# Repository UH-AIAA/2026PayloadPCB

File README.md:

# 2026 Payload PCB
This repo stores kicad files and other resources for the 2026 Payload PCB. Once the board is finalized, the repo will be archived.

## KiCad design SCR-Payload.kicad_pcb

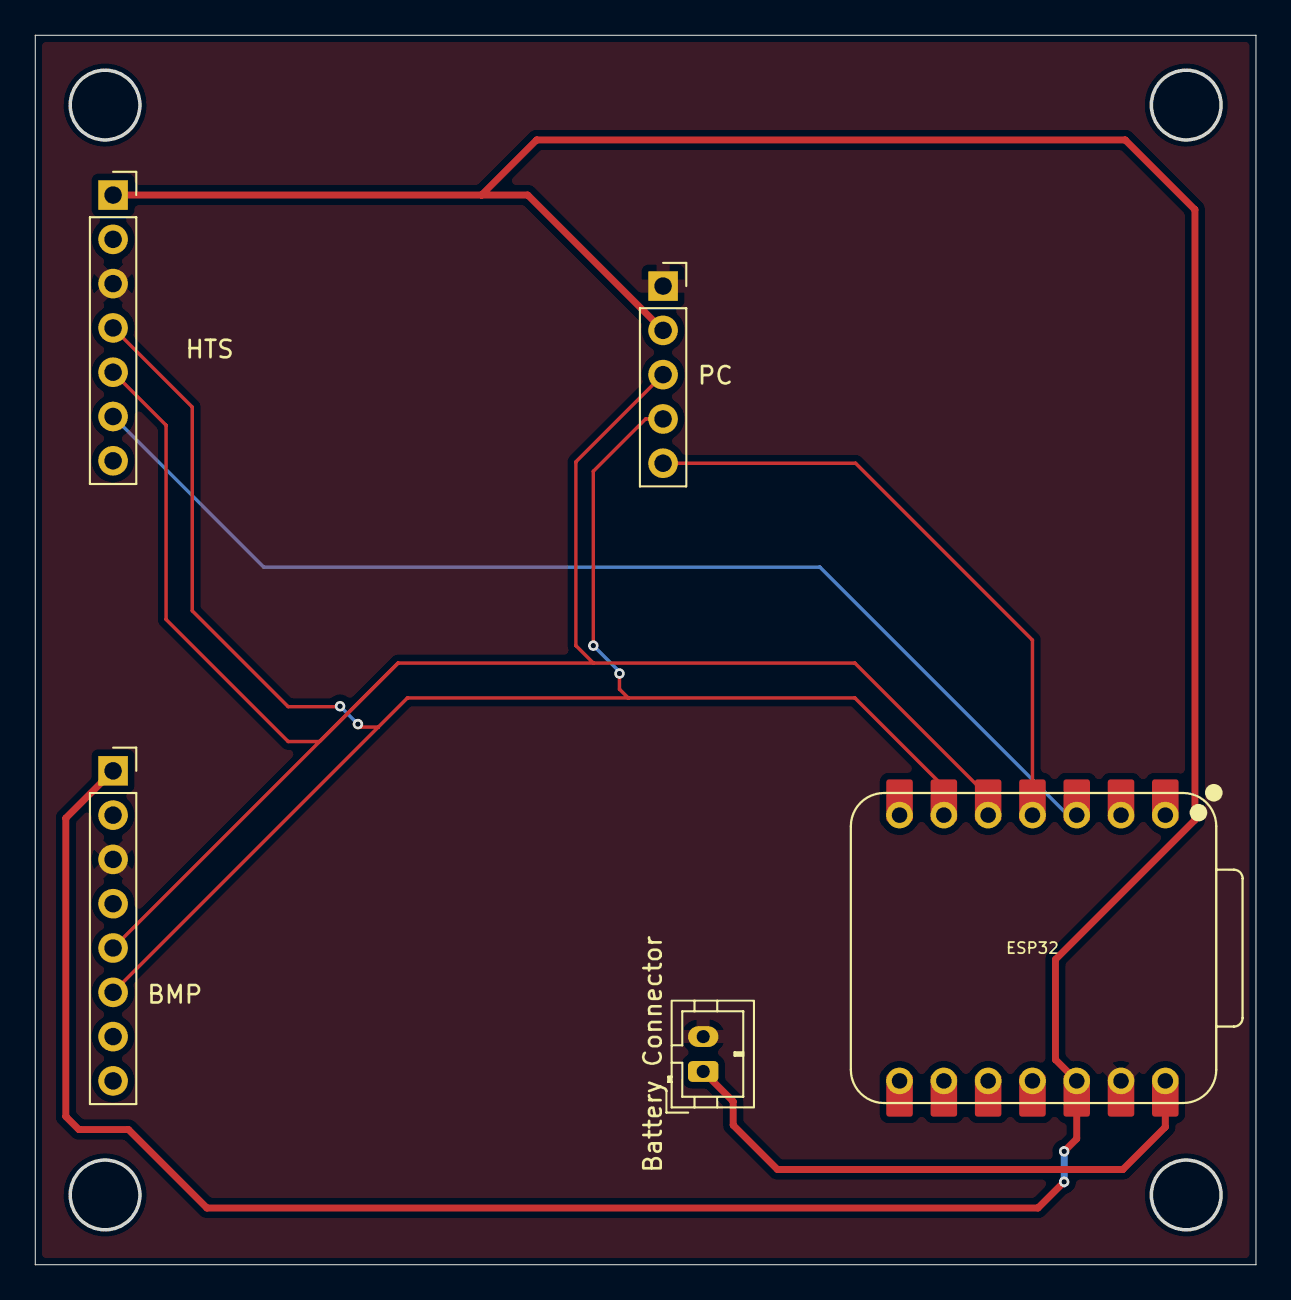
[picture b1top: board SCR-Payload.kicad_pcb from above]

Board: 2 copper layers, 69.9 x 70.4 mm, 5 parts (0 on the bottom side), 7 nets.

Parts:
BMP: Conn_01x08_Pin; PinSocket_1x08_P2.54mm_Vertical
Battery Connector: Conn_01x02_Pin; JST_PH_B2B-PH-K_1x02_P2.00mm_Vertical
ESP32: XIAO-ESP32-S3-DIP
HTS: Conn_01x07_Pin; PinSocket_1x07_P2.54mm_Vertical
PC: Conn_01x05_Pin; PinSocket_1x05_P2.54mm_Vertical

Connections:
+3.3V: BMP.1, ESP32.12 (3V3), HTS.1, PC.2
GND: BMP.3, Battery Connector.2, ESP32.13 (GND), HTS.3, PC.1
HTS DR: ESP32.3 (GPIO3_A2_D2), HTS.6
I2C SCL: BMP.6, ESP32.6 (GPIO6_A5_D5_SCL), HTS.4, PC.4
I2C SDA: BMP.5, ESP32.5 (GPIO5_A4_D4_SDA), HTS.5, PC.3
RTC SQW: ESP32.4 (GPIO4_A3_D3), PC.5
VCC: Battery Connector.1, ESP32.14 (VBUS)

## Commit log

2026-05-28 initial commit, adding .gitignore
2026-05-28 first complete design of board
2026-05-28 added readme
